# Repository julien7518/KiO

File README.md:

# 🚗 KiO – Mini voiture avec détection de mur

KiO est un projet de mini voiture équipée d’un capteur à ultrasons.  
Elle est capable de mesurer la distance face à un obstacle et de s’arrêter automatiquement.  
Un écran affiche en temps réel la distance mesurée, et une LED change de couleur en fonction de la proximité.

---

## ✨ Fonctionnalités
- Détection des obstacles  
- Arrêt automatique à 10 cm du mur  
- Affichage de la distance en temps réel sur écran  
- Indicateur lumineux avec LED RGB :  
  - 🔵 Bleu : > 30 cm (avance)  
  - 🟢 Vert : 15–30 cm (avance)  
  - 🟡 Jaune : 10–15 cm (arrêt)  
  - 🔴 Rouge : < 10 cm (recule)  

---

## 📂 Structure du projet
```
KiO/
├── code/
     ├── KiO/       # Code Arduino pour la gestion du capteur, LED, écran et logique d'arrêt
├── footprints/     # Empreintes utilisées dans KiCad pour le PCB
├── symbols/        # Symboles électroniques pour KiCad
└── README.md       # Documentation du projet
```

---

## 🛠️ Électronique utilisé
- Microcontrôleur : **Seeed XIAO ESP32S3**  
- Capteur ultrason : **HC-SR04**  
- Écran : **SSD 1306**  
- Double pont en H : **L293D**
- LED RGB 4 broches  
- Moteur DC double axe 1:48

---

## 📸 Modélisation
Les schémas électroniques et la modélisation du PCB ont été réalisés avec **KiCad**.  
- Les symboles personnalisés sont dans le dossier `symbols`.  
- Les empreintes personnalisées sont dans le dossier `footprints`.

---

## 🚀 Mise en route
1. Cloner le projet :  
   ```bash
   git clone https://github.com/julien7518/KiO.git
   ```
2. Ouvrir le dossier `code/` dans l’IDE Arduino.  
3. Sélectionner la carte Arduino correspondante.  
4. Compiler et téléverser le code.  
5. Connecter la voiture et tester la détection de mur.  

---

## 📜 Licence
Ce projet est distribué sous licence MIT – voir le fichier [LICENSE](LICENSE) pour plus de détails.

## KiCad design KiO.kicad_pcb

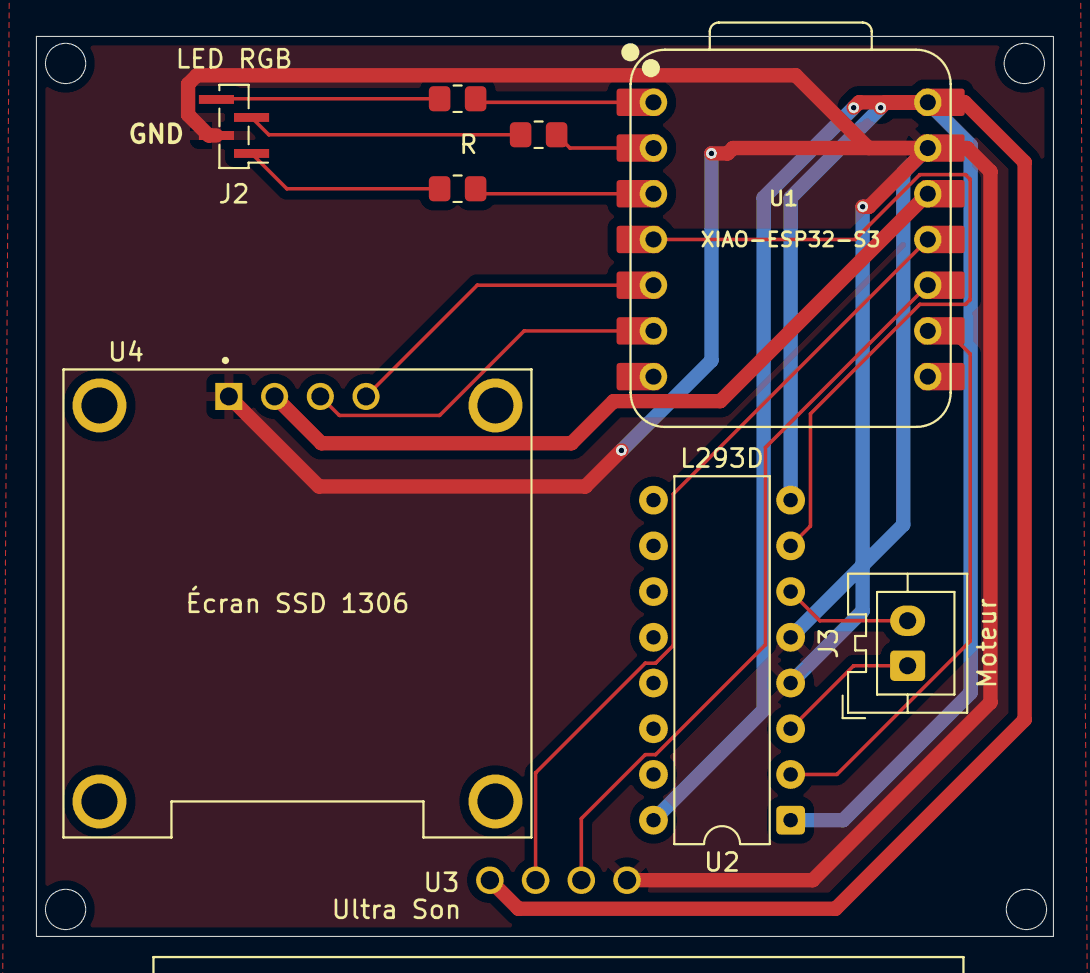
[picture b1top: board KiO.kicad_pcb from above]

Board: 2 copper layers, 56.5 x 50.0 mm, 9 parts (0 on the bottom side), 17 nets.

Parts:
J2: LED RGB; PinSocket_1x04_P1.00mm_Vertical_SMD_Pin1Left
J3: Moteur; JST_XA_B02B-XASK-1_1x02_P2.50mm_Vertical
R, R2, R3: R; R_0805_2012Metric_Pad1.20x1.40mm_HandSolder
U1: XIAO-ESP32-S3; XIAO-ESP32S3-DIP
U2: L293D; DIP-16_W7.62mm
U3: Ultra Son; XCVR_HC-SR04
U4: Écran SSD 1306; MODULE_DM-OLED096-636

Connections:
+3.3V: U1.12 (VCC_3V3), U4.2 (VCC_IN)
GND: J2.2, U1.13 (GND), U2.4 (GND), U2.5 (GND), U3.4 (GND), U4.1 (GND)
unnamed: J2.1, R3.2
unnamed: J2.3, R2.2
unnamed: J2.4, R.2
unnamed: J3.1, U2.3 (1Y)
unnamed: J3.2, U2.6 (2Y)
unnamed: R.1, U1.1 (GPIO1/D0/A0)
unnamed: R2.1, U1.2 (GPIO2/DA/A1)
unnamed: R3.1, U1.3 (GPIO3/D2/A2)
unnamed: U1.4 (GPIO4/D3/A3), U2.7 (2A)
unnamed: U1.5 (GPIO5/D4/I2C_SDA), U4.4 (SDA)
unnamed: U1.9 (GPIO7/D8/A8/SCK), U2.2 (1A)
unnamed: U1.10 (GPIO8/D9/A9/MISO), U3.3 (ECHO)
unnamed: U1.6 (GPIO9/D5/I2C_SCL), U4.3 (SCL)
unnamed: U1.11 (GPIO9/D10/A10/MOSI), U3.2 (TRIG)
VCC: U1.14 (VBUS), U2.1 (EN1,2), U2.8 (VCC2), U2.16 (VCC1), U3.1 (VCC)

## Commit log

2025-09-19 fix screen display and connection
2025-09-19 fix directory structure
2025-09-19 fix pin connection in code
